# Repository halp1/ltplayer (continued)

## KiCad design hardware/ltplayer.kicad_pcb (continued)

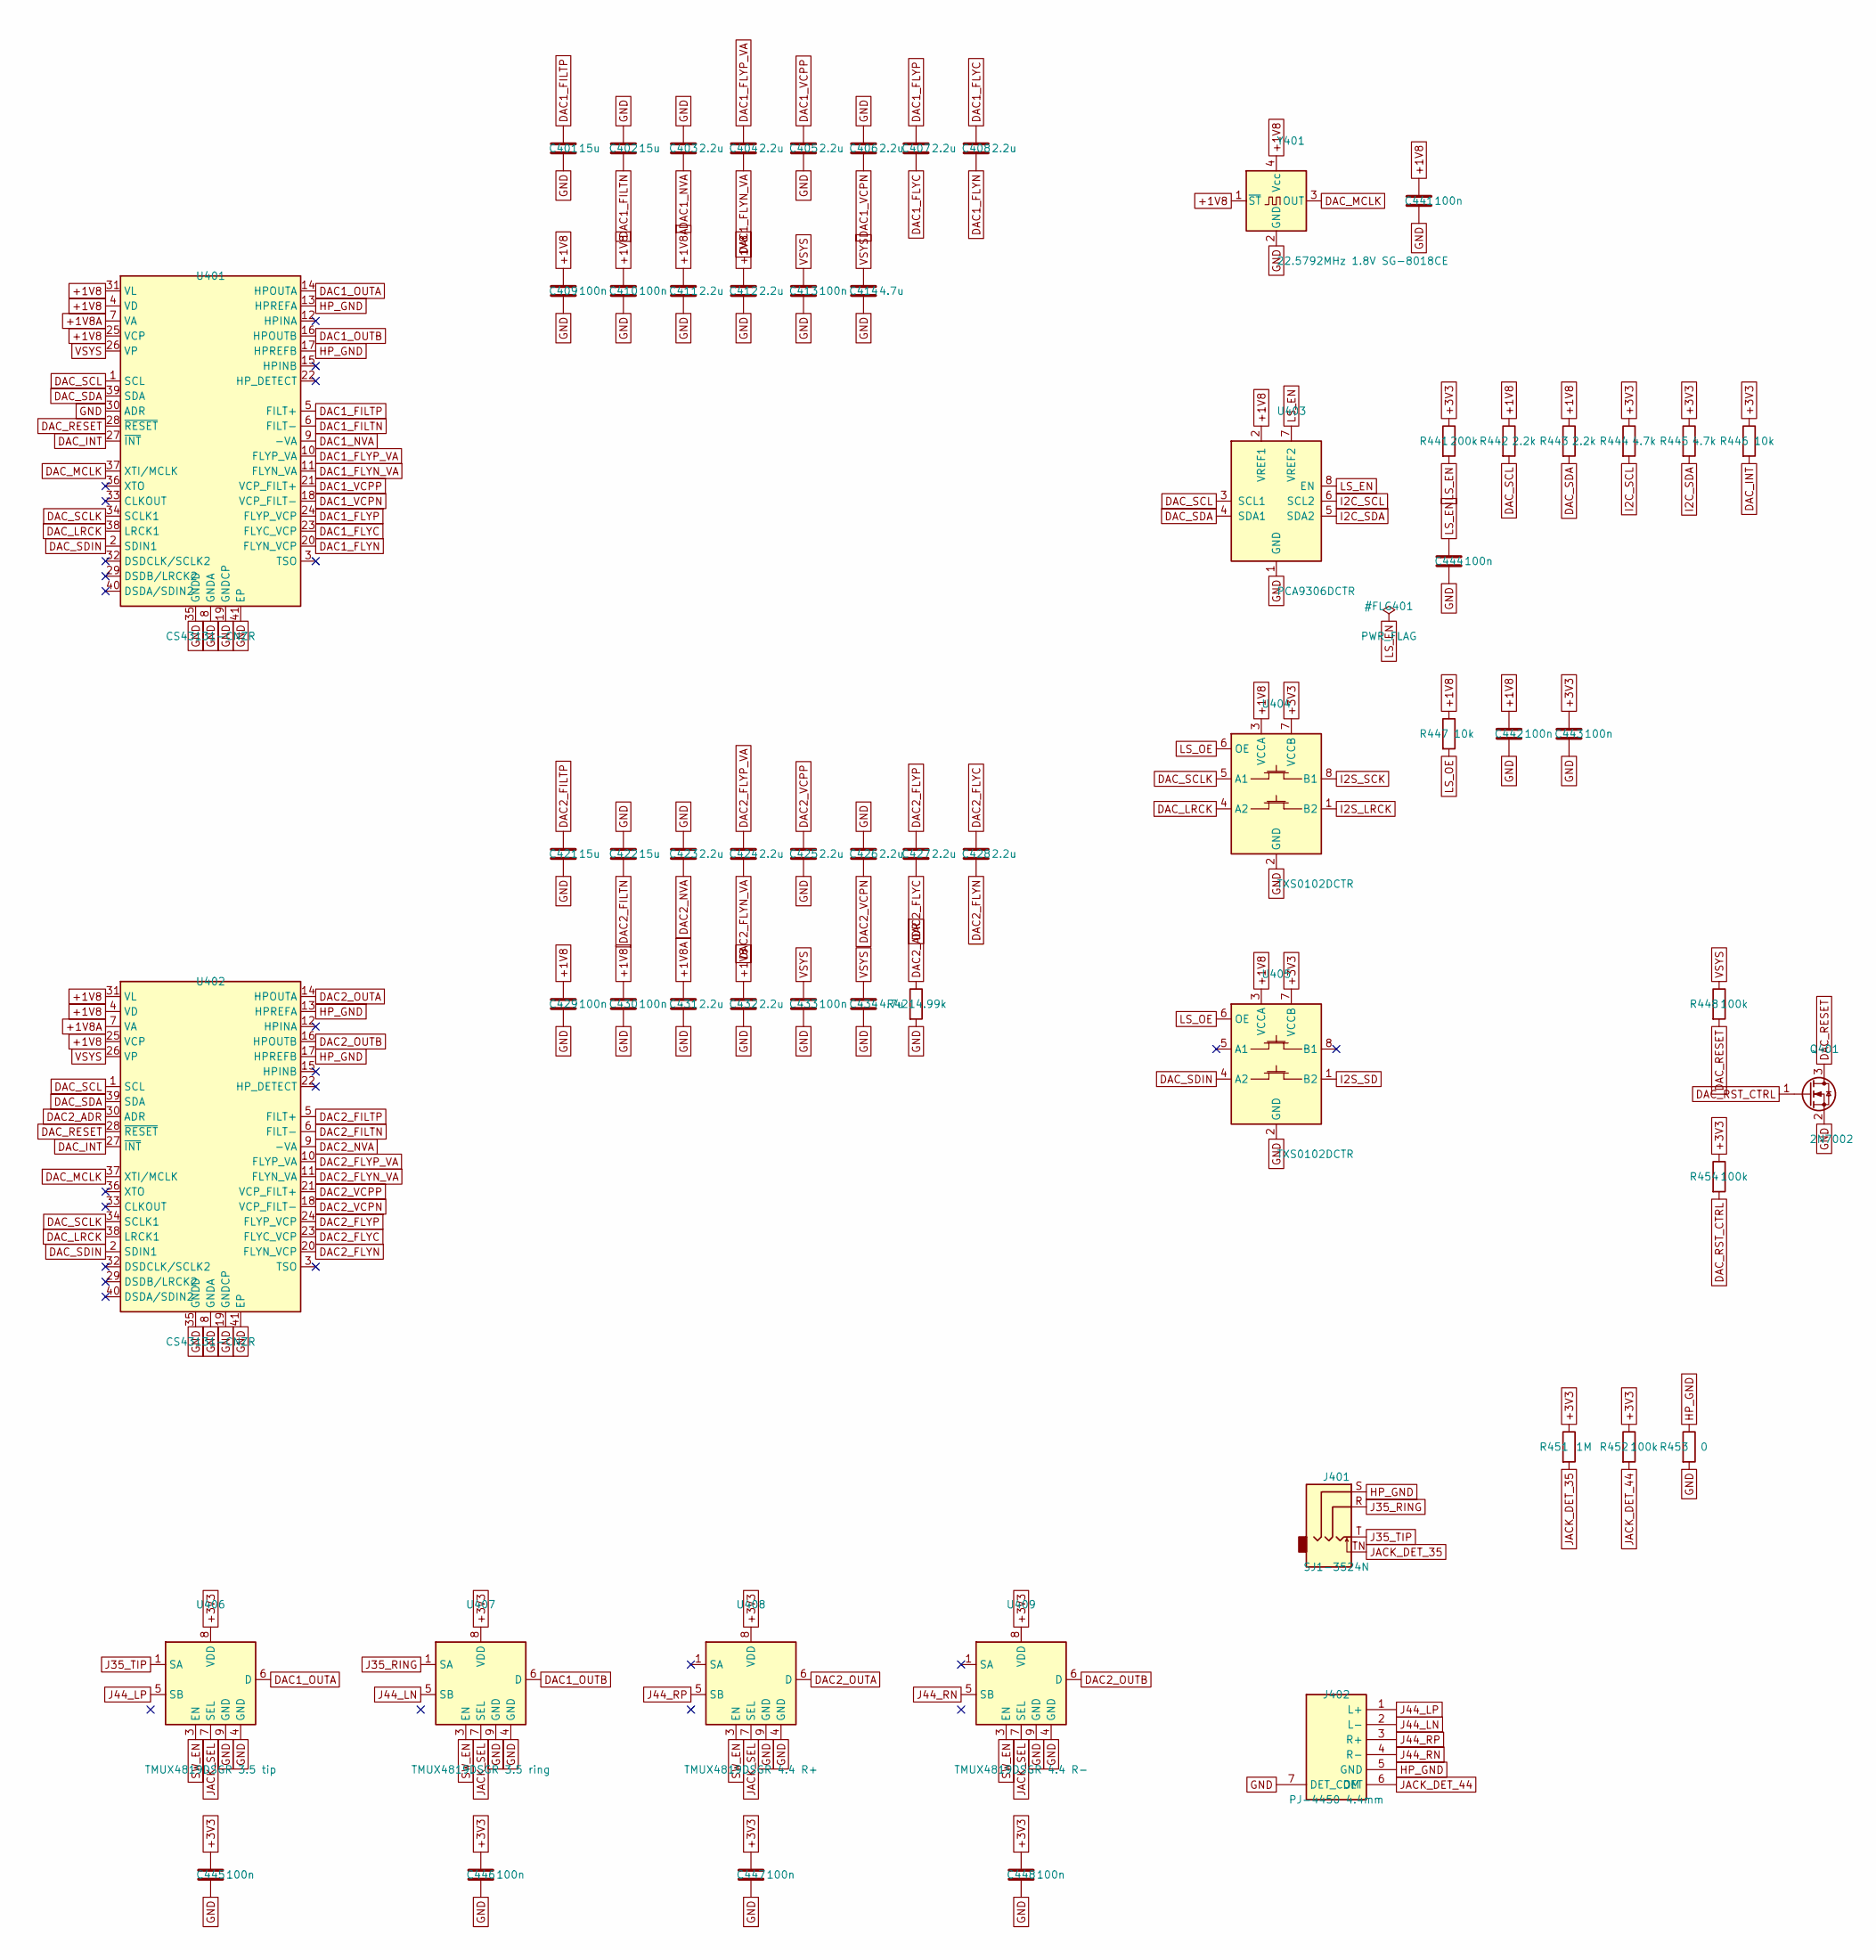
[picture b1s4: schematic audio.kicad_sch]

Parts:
C401, C402, C421, C422: 15u; C_0603_1608Metric
C403, C404, C405, C406, C407, C408, C411, C412, C423, C424, C425, C426, C427, C428, C431, C432: 2.2u; C_0603_1608Metric
C409, C410, C413, C429, C430, C433, C441, C442, C443, C444, C445, C446, C447, C448: 100n; C_0603_1608Metric
C414, C434: 4.7u; C_0603_1608Metric
J401: SJ1-3524N; Jack_3.5mm_CUI_SJ1-3524N_Horizontal
J402: PJ-4450 4.4mm; Jack_4.4mm_PJ-4450_Horizontal
Q401: 2N7002; SOT-23
R421: 4.99k; R_0603_1608Metric
R441: 200k; R_0603_1608Metric
R442, R443: 2.2k; R_0603_1608Metric
R444, R445: 4.7k; R_0603_1608Metric
R446, R447: 10k; R_0603_1608Metric
R448, R452, R454: 100k; R_0603_1608Metric
R451: 1M; R_0603_1608Metric
R453: 0; R_0603_1608Metric
U401, U402: CS43131-CNZR; QFN-40-1EP_5x5mm_P0.4mm_EP3.6x3.6mm_ThermalVias
U403: PCA9306DCTR; SSOP-8_2.95x2.8mm_P0.65mm
U404, U405: TXS0102DCTR; SSOP-8_2.95x2.8mm_P0.65mm
U406: TMUX4819DSGR 3.5 tip; Texas_DSG0008A_WSON-8-1EP_2x2mm_P0.5mm_EP0.9x1.6mm_ThermalV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
U407: TMUX4819DSGR 3.5 ring; Texas_DSG0008A_WSON-8-1EP_2x2mm_P0.5mm_EP0.9x1.6mm_ThermalV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
U408: TMUX4819DSGR 4.4 R+; Texas_DSG0008A_WSON-8-1EP_2x2mm_P0.5mm_EP0.9x1.6mm_ThermalV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
U409: TMUX4819DSGR 4.4 R-; Texas_DSG0008A_WSON-8-1EP_2x2mm_P0.5mm_EP0.9x1.6mm_ThermalV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
Y401: 22.5792MHz 1.8V SG-8018CE; Oscillator_SMD_Abracon_ASE-4Pin_3.2x2.5mm

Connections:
+1V8: C409.1, C410.1, C412.1, C429.1, C430.1, C432.1, C441.1, C442.1, R442.1, R443.1, R447.1, U401.4 (VD), U401.25 (VCP), U401.31 (VL), U402.4 (VD), U402.25 (VCP), U402.31 (VL), U403.2 (VREF1), U404.3 (VCCA), U405.3 (VCCA), Y401.1 (~ST), Y401.4 (Vcc); also elsewhere on the board
+1V8A: C411.1, C431.1, U401.7 (VA), U402.7 (VA); also elsewhere on the board
+3V3: C443.1, C445.1, C446.1, C447.1, C448.1, R441.1, R444.1, R445.1, R446.1, R451.1, R452.1, R454.1, U404.7 (VCCB), U405.7 (VCCB), U406.8 (VDD), U407.8 (VDD), U408.8 (VDD), U409.8 (VDD); also elsewhere on the board
DAC1_FILTN: C402.2, U401.6 (FILT-)
DAC1_FILTP: C401.1, U401.5 (FILT+)
DAC1_FLYC: C407.2, C408.1, U401.23 (FLYC_VCP)
DAC1_FLYN: C408.2, U401.20 (FLYN_VCP)
DAC1_FLYN_VA: C404.2, U401.11 (FLYN_VA)
DAC1_FLYP: C407.1, U401.24 (FLYP_VCP)
DAC1_FLYP_VA: C404.1, U401.10 (FLYP_VA)
DAC1_NVA: C403.2, U401.9 (-VA)
DAC1_OUTA: U401.14 (HPOUTA), U406.6 (D)
DAC1_OUTB: U401.16 (HPOUTB), U407.6 (D)
DAC1_VCPN: C406.2, U401.18 (VCP_FILT-)
DAC1_VCPP: C405.1, U401.21 (VCP_FILT+)
DAC2_ADR: R421.1, U402.30 (ADR)
DAC2_FILTN: C422.2, U402.6 (FILT-)
DAC2_FILTP: C421.1, U402.5 (FILT+)
DAC2_FLYC: C427.2, C428.1, U402.23 (FLYC_VCP)
DAC2_FLYN: C428.2, U402.20 (FLYN_VCP)
DAC2_FLYN_VA: C424.2, U402.11 (FLYN_VA)
DAC2_FLYP: C427.1, U402.24 (FLYP_VCP)
DAC2_FLYP_VA: C424.1, U402.10 (FLYP_VA)
DAC2_NVA: C423.2, U402.9 (-VA)
DAC2_OUTA: U402.14 (HPOUTA), U408.6 (D)
DAC2_OUTB: U402.16 (HPOUTB), U409.6 (D)
DAC2_VCPN: C426.2, U402.18 (VCP_FILT-)
DAC2_VCPP: C425.1, U402.21 (VCP_FILT+)
DAC_INT: R446.2, U401.27 (~INT), U402.27 (~INT); also elsewhere on the board
DAC_LRCK: U401.38 (LRCK1), U402.38 (LRCK1), U404.4 (A2)
DAC_MCLK: U401.37 (XTI/MCLK), U402.37 (XTI/MCLK), Y401.3 (OUT)
DAC_RESET: Q401.3 (D), R448.2, U401.28 (~RESET), U402.28 (~RESET)
DAC_RST_CTRL: Q401.1 (G), R454.2; also elsewhere on the board
DAC_SCL: R442.2, U401.1 (SCL), U402.1 (SCL), U403.3 (SCL1)
DAC_SCLK: U401.34 (SCLK1), U402.34 (SCLK1), U404.5 (A1)
DAC_SDA: R443.2, U401.39 (SDA), U402.39 (SDA), U403.4 (SDA1)
DAC_SDIN: U401.2 (SDIN1), U402.2 (SDIN1), U405.4 (A2)
GND: C401.2, C402.1, C403.1, C405.2, C406.1, C409.2, C410.2, C411.2, C412.2, C413.2, C414.2, C421.2, C422.1, C423.1, C425.2, C426.1, C429.2, C430.2, C431.2, C432.2, C433.2, C434.2, C441.2, C442.2, C443.2, C444.2, C445.2, C446.2, C447.2, C448.2, J402.7 (DET_COM), Q401.2 (S), R421.2, R453.2, U401.8 (GNDA), U401.19 (GNDCP), U401.30 (ADR), U401.35 (GNDD), U401.41 (EP), U402.8 (GNDA), U402.19 (GNDCP), U402.35 (GNDD), U402.41 (EP), U403.1 (GND), U404.2 (GND), U405.2 (GND), U406.4 (GND), U406.9 (GND), U407.4 (GND), U407.9 (GND), U408.4 (GND), U408.9 (GND), U409.4 (GND), U409.9 (GND), Y401.2 (GND); also elsewhere on the board
HP_GND: J401.S, J402.5 (GND), R453.1, U401.13 (HPREFA), U401.17 (HPREFB), U402.13 (HPREFA), U402.17 (HPREFB)
I2C_SCL: R444.2, U403.6 (SCL2); also elsewhere on the board
I2C_SDA: R445.2, U403.5 (SDA2); also elsewhere on the board
I2S_LRCK: U404.1 (B2); also elsewhere on the board
I2S_SCK: U404.8 (B1); also elsewhere on the board
I2S_SD: U405.1 (B2); also elsewhere on the board
J35_RING: J401.R, U407.1 (SA)
J35_TIP: J401.T, U406.1 (SA)
J44_LN: J402.2 (L-), U407.5 (SB)
J44_LP: J402.1 (L+), U406.5 (SB)
J44_RN: J402.4 (R-), U409.5 (SB)
J44_RP: J402.3 (R+), U408.5 (SB)
JACK_DET_35: J401.TN, R451.2; also elsewhere on the board
JACK_DET_44: J402.6 (DET), R452.2; also elsewhere on the board
JACK_SEL: U406.7 (SEL), U407.7 (SEL), U408.7 (SEL), U409.7 (SEL); also elsewhere on the board
LS_EN: C444.1, R441.2, U403.7 (VREF2), U403.8 (EN)
LS_OE: R447.2, U404.6 (OE), U405.6 (OE)
SW_EN: U406.3 (EN), U407.3 (EN), U408.3 (EN), U409.3 (EN); also elsewhere on the board
VSYS: C413.1, C414.1, C433.1, C434.1, R448.1, U401.26 (VP), U402.26 (VP); also elsewhere on the board

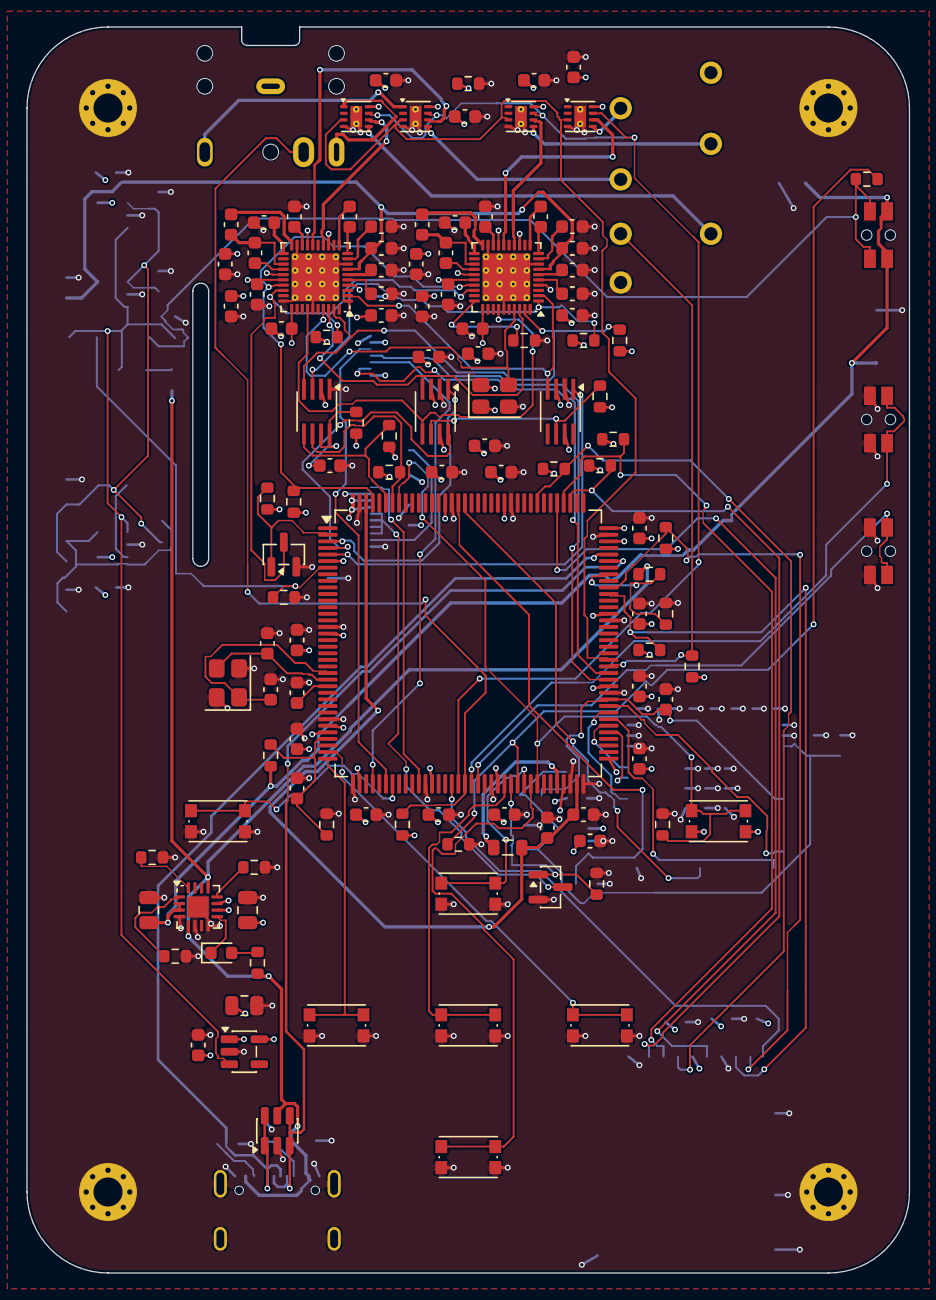
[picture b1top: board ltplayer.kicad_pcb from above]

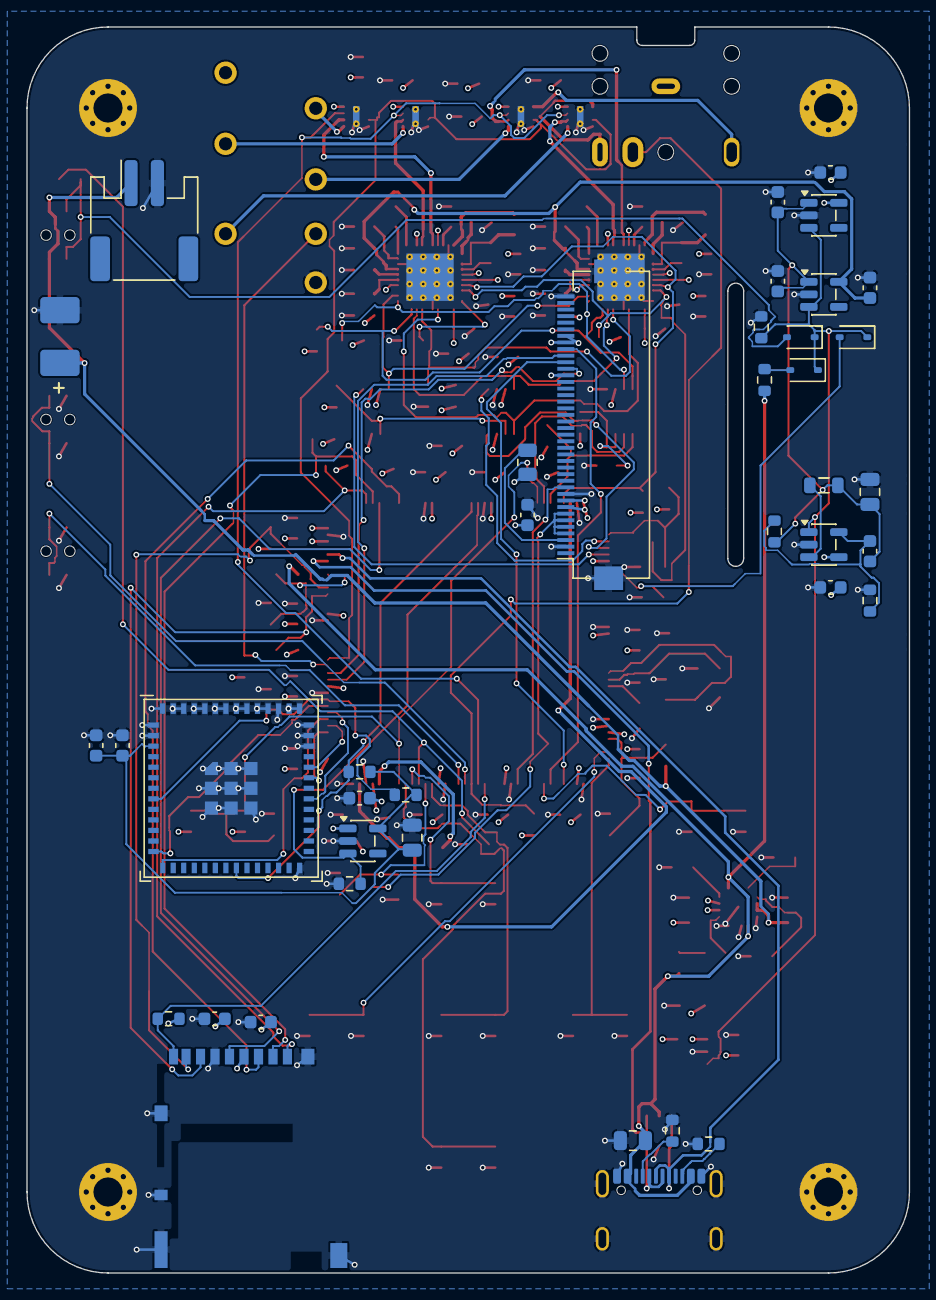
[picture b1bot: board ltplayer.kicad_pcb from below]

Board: 4 copper layers, 67.0 x 94.6 mm, 165 parts (42 on the bottom side), 116 nets.

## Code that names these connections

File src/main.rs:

#![no_std]
#![no_main]

use defmt_rtt as _;
use embassy_executor::Spawner;
use embassy_stm32::bind_interrupts;
use embassy_stm32::gpio::{Input, Level, Output, Pull, Speed};
use embassy_stm32::peripherals::SDMMC1;
use embassy_stm32::sdmmc::InterruptHandler;
use embassy_stm32::{spi, time::Hertz};
use embassy_time::Timer;
use panic_probe as _;
use static_cell::StaticCell;

pub mod audio;
pub mod controls;
pub mod file_manager;
pub mod jack;
pub mod playback;
pub mod renderer;
pub mod state;

bind_interrupts!(struct Irqs {
  SDMMC1 => InterruptHandler<SDMMC1>;
});

static SDMMC: StaticCell<embassy_stm32::sdmmc::Sdmmc<'static>> = StaticCell::new();
static FS_CELL: StaticCell<file_manager::FS<'static, 'static>> = StaticCell::new();

#[embassy_executor::main]
async fn main(spawner: Spawner) -> ! {
  let mut config = embassy_stm32::Config::default();
  config.rcc.msis = Some(embassy_stm32::rcc::MSIRange::RANGE_48MHZ);
  config.rcc.msik = Some(embassy_stm32::rcc::MSIRange::RANGE_48MHZ);
  let p = embassy_stm32::init(config);

  let sdmmc = SDMMC.init(embassy_stm32::sdmmc::Sdmmc::new_4bit(
    p.SDMMC1,
    Irqs,
    p.PC12,
    p.PD2,
    p.PC8,
    p.PC9,
    p.PC10,
    p.PC11,
    Default::default(),
  ));

  let fs = FS_CELL.init(
    microsd::mount(sdmmc, microsd::SdCardConfig::default())
      .await
      .expect("SD card mount failed"),
  );

  defmt::info!("sd up");

  let _touch_cs = Output::new(p.PF13, Level::High, Speed::Low);
  let _sd_cs = Output::new(p.PF14, Level::High, Speed::Low);
  let _memory_cs = Output::new(p.PE9, Level::High, Speed::Low);

  let cs = Output::new(p.PD14, Level::High, Speed::High);
  let dc = Output::new(p.PD15, Level::Low, Speed::High);
  let rst = Output::new(p.PF12, Level::High, Speed::High);
  let _backlight = Output::new(p.PE11, Level::High, Speed::Low);

  let mut display_spi_config = spi::Config::default();
  display_spi_config.frequency = Hertz::mhz(24);
  let spi = spi::Spi::new_blocking(p.SPI1, p.PA5, p.PA7, p.PA6, display_spi_config);

  let mut display_buffer = [0_u8; 2048];
  let display = display::new(spi, cs, dc, rst, &mut display_buffer).expect("Display init failed");

  defmt::info!("display up");

  let files = file_manager::list_files(fs)
    .await
    .expect("File listing failed");

  // TODO(pcb): placeholder pins until the PCB pinout is final. PE2 to PE6 are
  // kept free for SAI1 and PB8/PB9 for the DAC I2C.
  let jack_sel = Output::new(p.PG0, Level::Low, Speed::Low);
  let detect_35 = Input::new(p.PG1, Pull::Up);
  let detect_44 = Input::new(p.PG2, Pull::Up);

  spawner.spawn(jack::jack_task(detect_35, detect_44).unwrap());
  spawner.spawn(playback::playback_task(fs, files.clone(), jack_sel).unwrap());

  spawner.spawn(
    controls::controls_task(
      files.clone(),
      Input::new(p.PA3, Pull::Up),
      Input::new(p.PA2, Pull::Up),
      Input::new(p.PC3, Pull::Up),
      Input::new(p.PB0, Pull::Up),
    )
    .unwrap(),
  );

  let mut renderer = renderer::Renderer::new(display);

  defmt::info!("ready to start");

  let mut last_state: Option<state::State> = None;

  loop {
    let current_state = { *state::STATE.lock().await };

    match (last_state, current_state) {
      (None, state::State::Menu(idx)) => {
        renderer.clear().unwrap();
        renderer.render_file_list(files.as_slice(), idx).unwrap();
        last_state = Some(current_state);
      }
      (Some(state::State::Menu(prev_idx)), state::State::Menu(curr_idx)) => {
        if prev_idx != curr_idx {
          renderer.render_file_list(files.as_slice(), curr_idx).unwrap();
          last_state = Some(current_state);
        }
      }
      (Some(state::State::Menu(_)), state::State::Playing(p))
      | (None, state::State::Playing(p)) => {
        renderer.clear().unwrap();
        renderer
          .render_player(files[p.index].as_str(), p.elapsed, p.total, p.is_playing)
          .unwrap();
        last_state = Some(current_state);
      }
      (Some(state::State::Playing(_)), state::State::Menu(idx)) => {
        renderer.clear().unwrap();
        renderer.render_file_list(files.as_slice(), idx).unwrap();
        last_state = Some(current_state);
      }
      (Some(state::State::Playing(prev_p)), state::State::Playing(curr_p)) => {
        if prev_p.index != curr_p.index {
          renderer.clear().unwrap();
          renderer
            .render_player(
              files[curr_p.index].as_str(),
              curr_p.elapsed,
              curr_p.total,
              curr_p.is_playing,
            )
            .unwrap();
        } else {
          if prev_p.elapsed != curr_p.elapsed {
            renderer
              .update_progress(curr_p.elapsed, curr_p.total)
              .unwrap();
          }
          if prev_p.is_playing != curr_p.is_playing {
            renderer.update_play_pause(curr_p.is_playing).unwrap();
          }
        }
        last_state = Some(current_state);
      }
    }

    Timer::after_millis(30).await;
  }
}
